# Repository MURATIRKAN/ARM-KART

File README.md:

//*********************************//
ELEKTRONİK SİSTEM TASARIM ÇALIŞMALARI //
GELİŞTİRME KARTLARI-YAZILIM.     //
MURAT IRKAN 2021-2023            //
muratir1975@windowslive.com      //
***********************************

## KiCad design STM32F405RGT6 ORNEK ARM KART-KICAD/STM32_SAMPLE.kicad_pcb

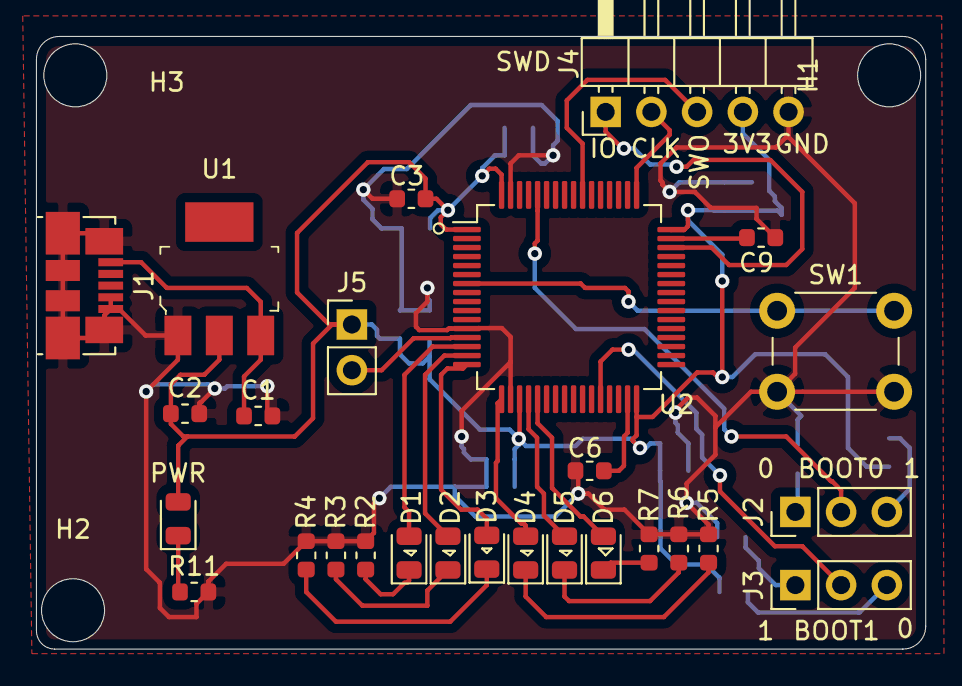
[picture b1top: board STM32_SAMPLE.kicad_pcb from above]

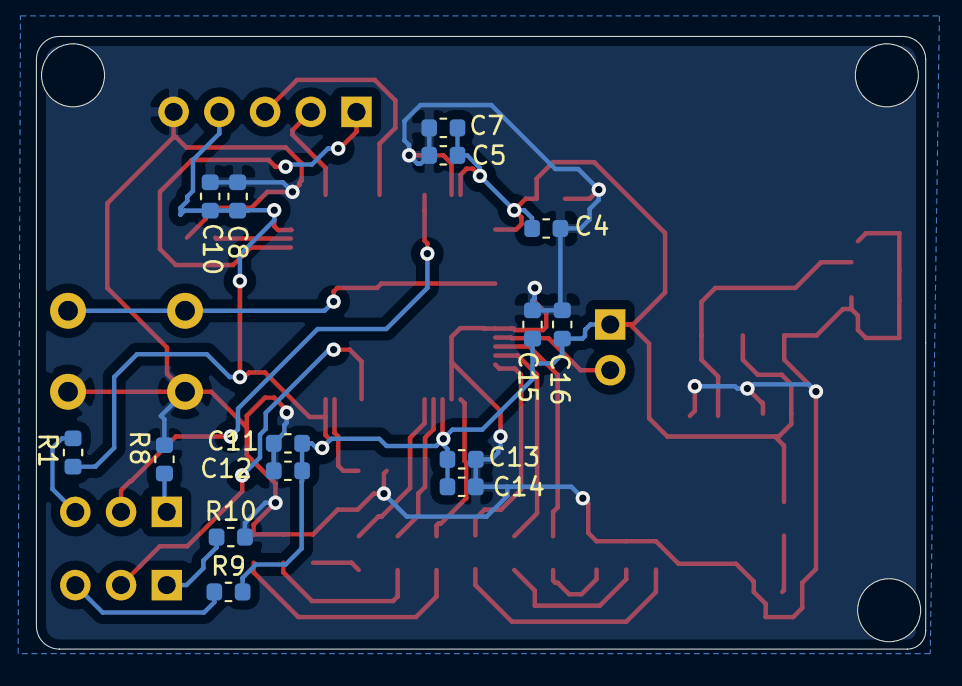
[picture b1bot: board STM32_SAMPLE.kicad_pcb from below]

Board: 2 copper layers, 49.4 x 34.0 mm, 45 parts (15 on the bottom side), 29 nets.

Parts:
C1, C2, C3: 10uF; C_0603_1608Metric
C4, C5, C7, C8, C10, C11, C12, C13, C14, C15: 100nF; C_0603_1608Metric
C6, C9: 2.2uF; C_0603_1608Metric
C16: 1uF; C_0603_1608Metric
D1, D2, D3, D4, D5, D6: LED; LED_0805_2012Metric
H1, H2, H3: MountingHole; MountingHole_3.5mm
J1: USB_B_Micro; USB_Micro-B_Molex_47346-0001
J2, J3: Conn_01x03_Male; PinHeader_1x03_P2.54mm_Vertical
J4: Conn_01x05_Male; PinHeader_1x05_P2.54mm_Horizontal
J5: Conn_01x02_Male; PinHeader_1x02_P2.54mm_Vertical
PWR: LED; LED_0805_2012Metric
R1, R8, R9, R10: 10K; R_0603_1608Metric
R2, R3, R4, R5, R6, R7, R11: 220ohms; R_0603_1608Metric
SW1: SW_Push; SW_PUSH_6mm_H5mm
U1: LM1117-3.3; SOT-223
U2: STM32F405RGTx; LQFP-64_10x10mm_P0.5mm

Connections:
+3V3: C2.1, C3.1, C4.1, C5.1, C7.1, C8.1, C10.1, C11.1, C12.1, C13.1, C14.1, C15.1, C16.1, J4.4, J5.1, PWR.2, R1.2, R9.2, U1.2, U2.1, U2.19, U2.32, U2.48, U2.64
+5V: C1.1, J1.1, U1.3
BOOT0: J2.2, U2.60
BOOT1: J3.2, U2.28
GND: C1.2, C2.2, C3.2, C4.2, C5.2, C6.2, C7.2, C8.2, C9.2, C10.2, C11.2, C12.2, C13.2, C14.2, C15.2, C16.2, J1.4, J1.5, J1.6, J4.5, R2.1, R3.1, R4.1, R5.1, R6.1, R7.1, R8.1, R10.2, R11.2, SW1.2, U1.1, U2.12, U2.18, U2.63
NRST: SW1.1, U2.7
unnamed: C6.1, U2.31
unnamed: C9.1, U2.47
unnamed: D1.1, R2.2
unnamed: D1.2, U2.14
unnamed: D2.1, R3.2
unnamed: D2.2, U2.15
unnamed: D3.1, R4.2
unnamed: D3.2, U2.16
unnamed: D4.1, R5.2
unnamed: D4.2, U2.17
unnamed: D5.1, R6.2
unnamed: D5.2, U2.20
unnamed: D6.1, R7.2
unnamed: D6.2, U2.21
unnamed: PWR.1, R11.1
unnamed: J2.1, R8.2
unnamed: J2.3, R1.1
unnamed: J3.1, R10.1
unnamed: J3.3, R9.1
SWDCLK: J4.2, U2.49
SWDIO: J4.1, U2.46
SWO: J4.3, U2.55
VDDA: J5.2, U2.13

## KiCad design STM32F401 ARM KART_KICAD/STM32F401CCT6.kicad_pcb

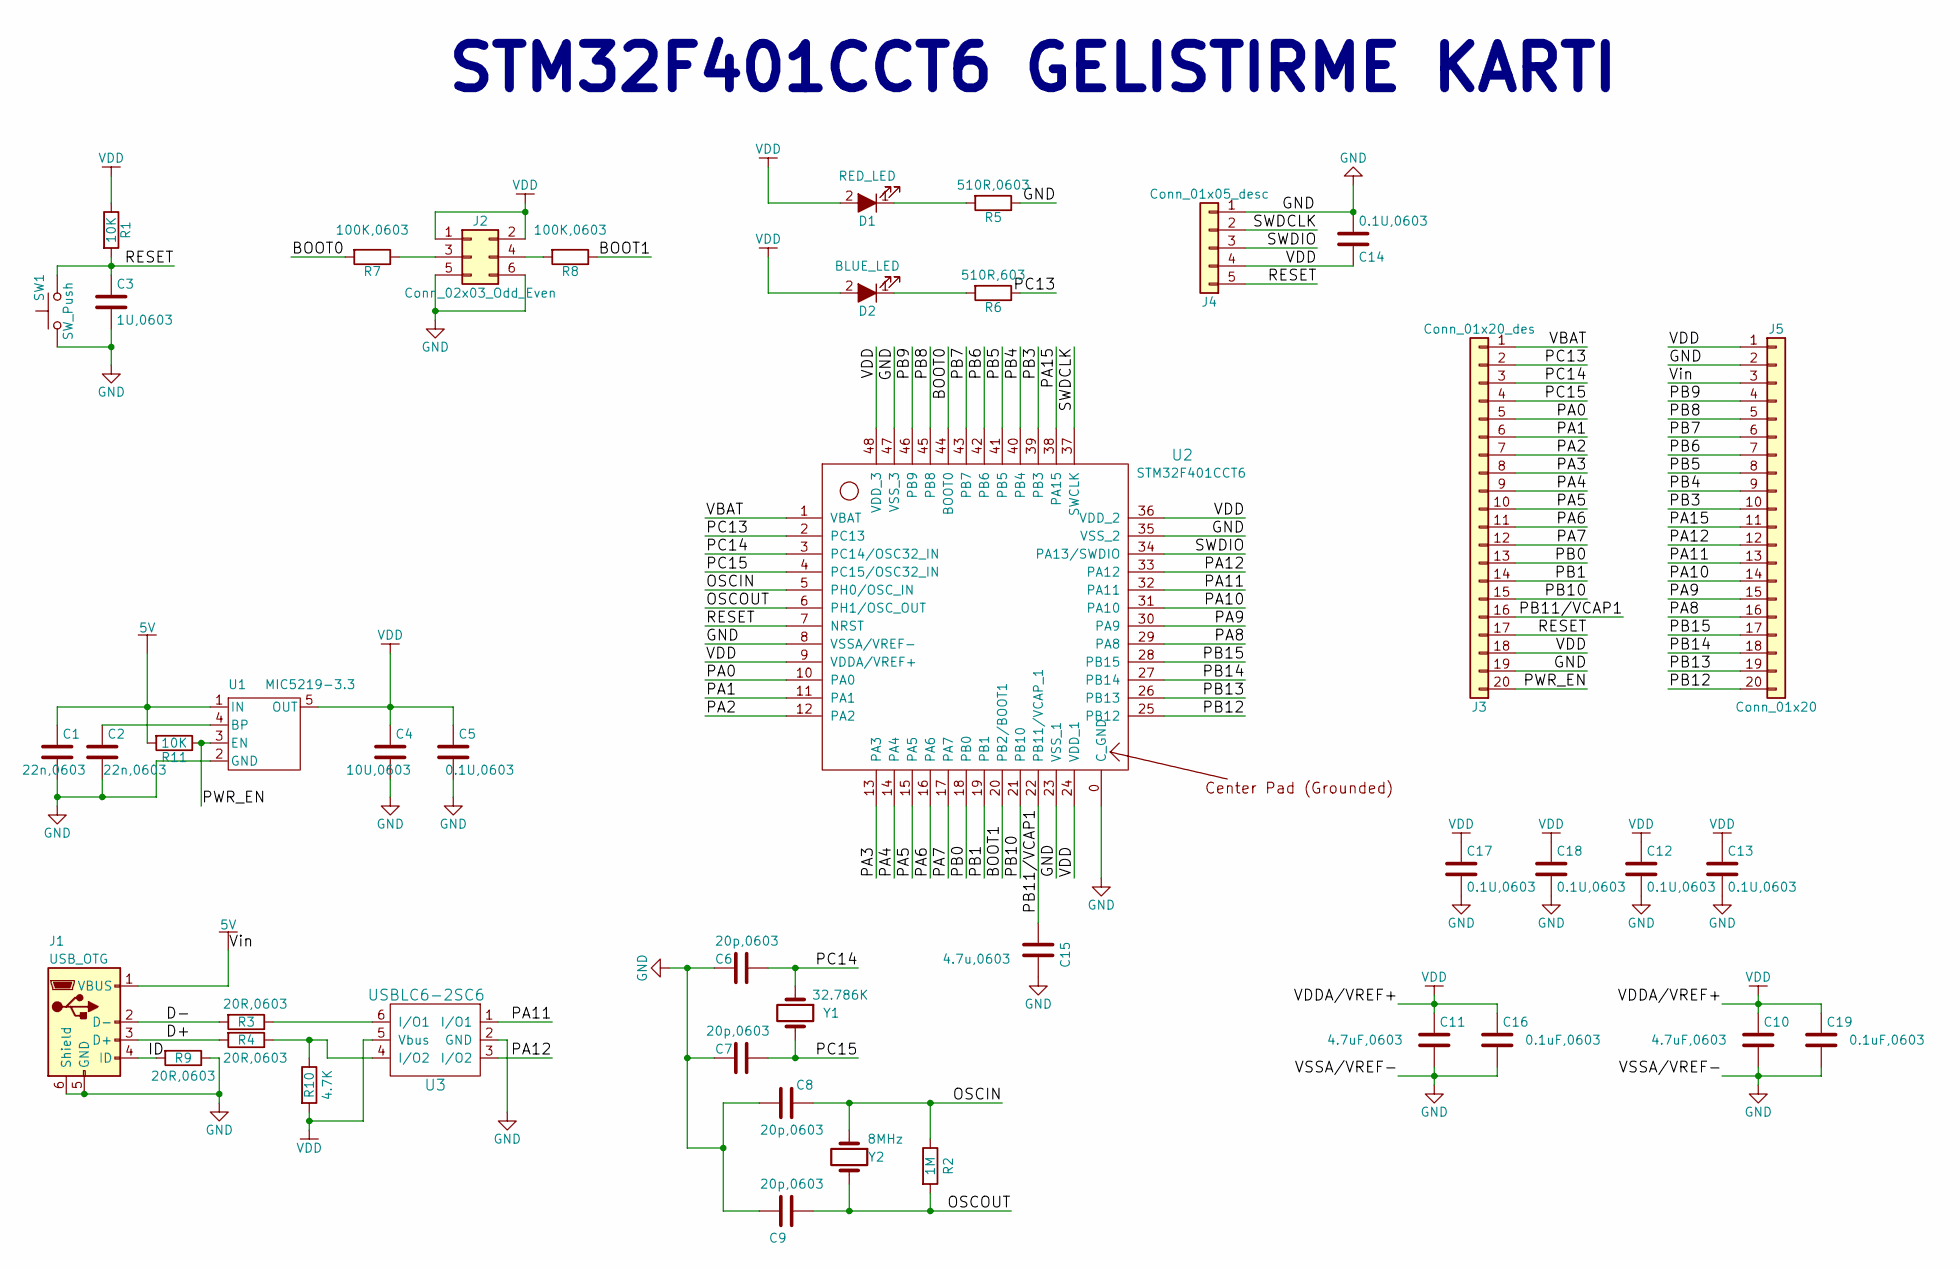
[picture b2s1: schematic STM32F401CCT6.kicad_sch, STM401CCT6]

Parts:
C1, C2: 22n,0603; C_0603
C3: 1U,0603; C_0603
C4: 10U,0603; C_0603
C5, C12, C13, C14, C17, C18: 0.1U,0603; C_0603
C6, C7, C8, C9: 20p,0603; C_0603
C10, C11: 4.7uF,0603; C_0603
C15: 4.7u,0603; C_0603
C16, C19: 0.1uF,0603; C_0603
D1: RED_LED; LED_0805
D2: BLUE_LED; LED_0805
J1: USB_OTG; USB_Micro-B_Molex-105017-0001
J2: Conn_02x03_Odd_Even; Pin_Header_Straight_2x03_Pitch2.54mm
J3: Conn_01x20_des; Pin_Header_Straight_1x20_Pitch2.54mm
J4: Conn_01x05_desc; Pin_Header_Angled_1x05_Pitch2.54mm
J5: Conn_01x20; Pin_Header_Straight_1x20_Pitch2.54mm
R1, R11: 10K; R_0603
R2: 1M; R_0603
R3, R4, R9: 20R,0603; R_0603
R5: 510R,0603; R_0603
R6: 510R,603; R_0603
R7, R8: 100K,0603; R_0603
R10: 4.7K; R_0603
SW1: SW_Push; SW_SPST_TL3342
U1: MIC5219-3.3; SOT-23-5
U2: STM32F401CCT6
U3: USBLC6-2SC6; SOT-23-6
Y1: 32.786K; Crystal_SMD_SeikoEpson_MC306-4pin_8.0x3.2mm
Y2: 8MHz; Crystal_HC49-4H_Vertical

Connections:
+5V: C1.1, J1.1 (VBUS), J5.3, R11.2, U1.1 (IN)
/BOOT0: R7.2, U2.44 (BOOT0)
/BOOT1: R8.1, U2.20 (PB2/BOOT1)
/D+: J1.3 (D+), R4.2
/D-: J1.2 (D-), R3.2
/ID: J1.4 (ID), R9.2
/OSCIN: C8.1, R2.1, U2.5 (PH0/OSC_IN), Y2.1
/OSCOUT: C9.1, R2.2, U2.6 (PH1/OSC_OUT), Y2.2
/PA0: J3.5, U2.10 (PA0)
/PA1: J3.6, U2.11 (PA1)
/PA2: J3.7, U2.12 (PA2)
/PA3: J3.8, U2.13 (PA3)
/PA4: J3.9, U2.14 (PA4)
/PA5: J3.10, U2.15 (PA5)
/PA6: J3.11, U2.16 (PA6)
/PA7: J3.12, U2.17 (PA7)
/PA8: J5.16, U2.29 (PA8)
/PA9: J5.15, U2.30 (PA9)
/PA10: J5.14, U2.31 (PA10)
/PA11: J5.13, U2.32 (PA11), U3.1 (I/O1)
/PA12: J5.12, U2.33 (PA12), U3.3 (I/O2)
/PA15: J5.11, U2.38 (PA15)
/PB0: J3.13, U2.18 (PB0)
/PB1: J3.14, U2.19 (PB1)
/PB3: J5.10, U2.39 (PB3)
/PB4: J5.9, U2.40 (PB4)
/PB5: J5.8, U2.41 (PB5)
/PB6: J5.7, U2.42 (PB6)
/PB7: J5.6, U2.43 (PB7)
/PB8: J5.5, U2.45 (PB8)
/PB9: J5.4, U2.46 (PB9)
/PB10: J3.15, U2.21 (PB10)
/PB11/VCAP1: C15.2, J3.16, U2.22 (PB11/VCAP_1)
/PB12: J5.20, U2.25 (PB12)
/PB13: J5.19, U2.26 (PB13)
/PB14: J5.18, U2.27 (PB14)
/PB15: J5.17, U2.28 (PB15)
/PC13: J3.2, R6.1, U2.2 (PC13)
/PC14: C6.1, J3.3, U2.3 (PC14/OSC32_IN), Y1.1
/PC15: C7.1, J3.4, U2.4 (PC15/OSC32_IN), Y1.2, Y1.4
/PWR_EN: J3.20, R11.1, U1.3 (EN)
/RESET: C3.1, J3.17, J4.5, R1.2, SW1.2, U2.7 (NRST)
/SWDCLK: J4.2, U2.37 (SWCLK)
/SWDIO: J4.3, U2.34 (PA13/SWDIO)
/VBAT: J3.1, U2.1 (VBAT)
/VDD: C4.1, C5.1, C10.1, C11.1, C12.1, C13.1, C14.1, C16.1, C17.1, C18.1, C19.1, D1.2 (A), D2.2 (A), J2.1, J2.2, J3.18, J4.4, J5.1, R1.1, R10.2, U1.5 (OUT), U2.9 (VDDA/VREF+), U2.24 (VDD_1), U2.36 (VDD_2), U2.48 (VDD_3), U3.5 (Vbus)
GND: C1.2, C2.2, C3.2, C4.2, C5.2, C6.2, C7.2, C8.2, C9.2, C10.2, C11.2, C12.2, C13.2, C14.2, C15.1, C16.2, C17.2, C18.2, C19.2, J1.5 (GND), J1.6 (Shield), J2.5, J2.6, J3.19, J4.1, J5.2, R5.1, R9.1, SW1.1, U1.2 (GND), U2.0 (C_GND), U2.8 (VSSA/VREF-), U2.23 (VSS_1), U2.35 (VSS_2), U2.47 (VSS_3), U3.2 (GND)
unnamed: C2.1, U1.4 (BP)
unnamed: D1.1 (K), R5.2
unnamed: D2.1 (K), R6.2
unnamed: J2.3, R7.1
unnamed: J2.4, R8.2
unnamed: R3.1, U3.6 (I/O1)
unnamed: R4.1, R10.1, U3.4 (I/O2)

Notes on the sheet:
STM32F401CCT6 GELISTIRME KARTI

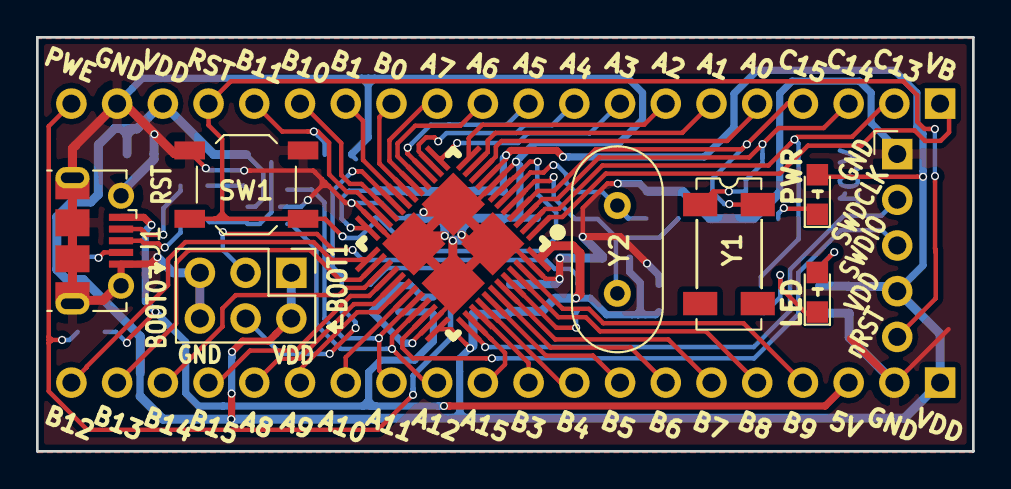
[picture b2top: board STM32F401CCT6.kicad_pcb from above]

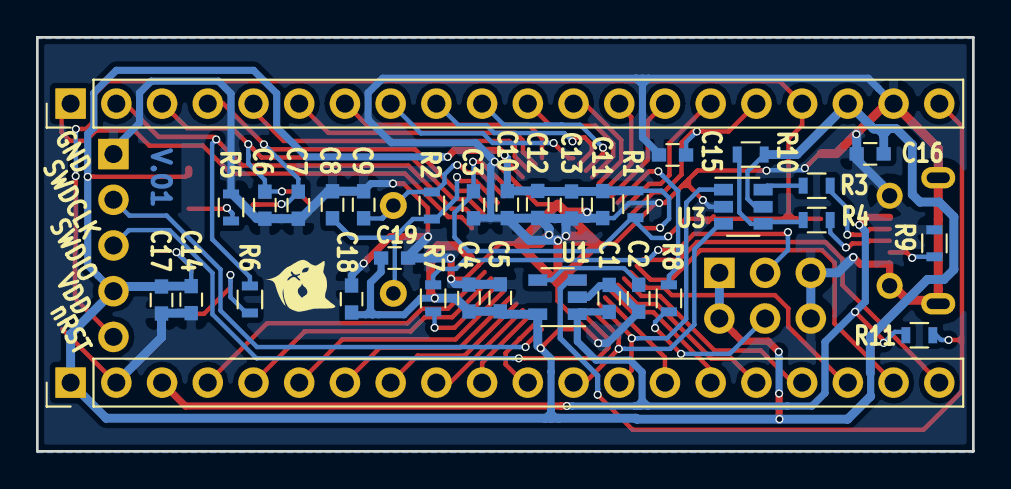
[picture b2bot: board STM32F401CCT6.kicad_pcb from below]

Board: 2 copper layers, 52.0 x 23.0 mm, 47 parts (35 on the bottom side), 54 nets.

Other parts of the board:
Dot: G***; Dot
HS_Crystal: G***; HS_Crystal
LS_Crystal: G***; LS_Crystal
Meow: G***; Meow

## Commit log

2022-09-24 STM32F401CCT6 ARM KART DİZAYN
    PCB VE ŞEMA.
    KİCAD ELEKTRONIK TASARIM PROGRAMI.
    https://www.kicad.org/
2022-09-24 STM32F042x6 ARM TEMEL KARTI
    NOT:KART PINLERI DEGISTIRILDI.!
2022-09-24 STM32F407 ARM GELISTIRME VE INTERNET KARTI
2022-09-24 STM32F042x6 SERİSİ DEMO KART DİZAYN.
    v.1.01
2022-09-26 STM32F405RGT6 ARM KART
2022-09-28 STM32F765VIT6 EAGLE VE DIP TRACE
    TASARLANIRKEN EAGLE TASARIM PROGRAMI VE DIP TRACE PROGRAMLARI KULLANILDI.
    1.https://diptrace.com/tr/
    2.https://www.autodesk.com/products/eagle/free-download
2022-09-29 STM32F401 ARM KEIL KOD
    ARM KEIL 6.18 DERLEYICI KULLANILDI.
2022-10-01 STM32F765VIT ARM KART V.1.02
    GUNCELLEME 9/1/2022
2022-10-02 STMF103CBT6 MINI ARM GELISTIRME KARTI
2022-10-02 stm32f103cbt6 pcb
2022-10-02 STM32F103 ZAMANLAMA VE LED KONTROL
    DERLEYICI KEIL ARM 6.18.
2022-10-08 STM32F103CBT6 TEMEL ARM KART
    ST MICROELEKTRONICS STM32F103CBT6 ARM - CORTEX M3 İŞLEMCİ
2022-10-08 STM32F103 ARM KEIL 6.18 DERLEYİCİ.
    STM32F103 ZAMANLAMA TEST KOD..
2022-10-08 STM32F103 ZAMANLAMA KODLARI.
    KEIL ARM VERSIYON 6.18
2022-10-08 STM32F042
2022-10-08 STM32F765VIT6 ARM CORTEX M7 DEMO.
2022-10-08 STM32F405RGT6 DEMO KART.KICAD TASARIM PROGRAMI.
2022-10-08 STM32F401 ARM CORTEX-M4 MINI
    STM32F401 ARM CORTEX-M4 MİNİ GELİŞTİRME KARTI
    V.1.02
2022-10-08 STM32F ARM KARTLAR.
2022-10-08 STM32F765VIT6 DEMO ARM KART
2022-10-14 STM32F103CBT6 MINI ARM GELİŞTİRME KARTI.
    V.1.01
    6/10/2022
2022-10-14 STM32F103CBT6 MİNİ ARM_CORTEX M3 GELİŞTİRME KARTI.
2022-10-14 STM32F103CBT6 MİNİ ARM CORTEX-M3 GELİŞTİRME KARTI.
    KART AUTODESK VEYA DIP TRACE İLE TASARLANMIŞTIR.
    V.1.02
2022-10-14 STM32F401 ARM GELİŞTİRME KARTI KICAD.
    KICAD ARM GELİŞTİRME KARTI DEMO.
2022-10-15 stm32f103cbt6 V.1.02
    MİNİ STM32F103CBT6 ARM KART...
2022-10-15 Delete STM32F103CBT6 ARM_KART directory
    DIPTRACE ELEKTRONIK TASARIM PROGRAMI
    STM32F103CBT6 PCB DEVRE TASARIMI..
2022-10-15 STM32F103CBT6:DIPTRACE TASARIM PROGRAMI v.1.02
    NOT:DEVRE USB DEN PROGRAMLANIR.STLINK ADAPTORU İLE.
2022-10-16 stm32f103cbt6 MİNİ ARM KART.(JTAG)
    GÜNCELLEME=JTAG-PROGRAMLAMA SOKETİ EKLENDİ.
    MİNİ JTAG SOKET..
2022-10-16 STM32F103CBT6 ARM GELİŞTİRME KARTI.
    JTAG PORTU VE GÜÇ LEDLERİ EKLENDİ.
2022-10-16 DIPTRACE TASARIM PROGRAMI.
    STM32F103CBT6 ARM-CORTEX M3 GELİŞTİRME KARTI.
    V.1.06 LEDLER VE JTAG SOKET EKLENDİ(MİNİ)
2022-10-17 STM32F103CBT6 DIPTRACE VE EAGLE TASARIM.
    MALZEME LİSTESİ EXCEL,GÜÇ LEDLERİ,MİNİ JTAG EKLENDİ.
    DELİKLER 2mm BOYUTUNDA TASARLANDI.
    V.1.07
2023-01-22 PIC18F44K22 KART
    PIC18F44K22 GELİŞTİRME KARTI..
2023-01-26 STM32F405RGT6V ARM KART
2023-01-26 yapay zeka tanıtımı
2023-01-30 STM32F405RGT6 ARM KART PCB
2023-01-30 STM32F405RGT6 AUTODESK EAGLE
2023-01-31 ARDUINO SICAKLIK VE ISIK TEST
2023-01-31 STM32F407 ARM VE INTERNET
2023-01-31 STM32F103CBT6 MINI ARM KART
    V.1.02
2023-01-31 ARDUINO SICAKLIK_ISIK KOD
2023-02-01 ARDUINO TOSHIBA TBN6612FNG MOTOR SURUCU
2023-02-01 ARDUINO BOSCH BME280 SENSOR
2023-02-01 STM32F405 VE 407 DOKUMAN
2023-02-01 ARDUINO DHT22 SENSOR
2023-02-01 STM32 LM35 VE LCD
2023-02-01 STM32F103 ARM KEIL LCD EKRAN
2023-02-01 STM32F103 AUTODESK EAGLE PCB VE SEMA
2023-02-01 arduıno l298 motor
2023-02-04 PIC18F44K22 KART
    MICRO-C ORNEK
2023-02-04 STMF103CBT6 ARM KART
2023-02-04 MICRO C PIC16 DC18B20 SENSOR
2023-02-07 STM32F405RGT6 ARM GELİŞTİRME KARTI
2023-02-07 PIC18F44K50 VE 45K50 GELİŞTİRME KARTI
2023-02-07 STM32F103CBT6 MINI ARM KART
2023-02-08 STM32F401CCT6 ARM VE ORNEK KiCad 6.0
2023-02-08 STM32F401CB PROTEUS VE KOD
2023-02-08 STM32F401CB KART/ARM KEIL KOD VE PROTEUS
2023-02-08 PIC16F877 MICRO_C LM35 SENSOR
2023-02-08 PIC18F44K22 VEYA PIC18F45K50 KART
    LM35 MICRO_C DERLEYICI
2023-02-08 STM32F407 ARM GELISTIRME VE INTERNET
2023-02-08 STM32F103CBT6 MINI ARM GELISTIRME KARTI
2023-02-08 STM32F401CB ARM GELISTIRME KARTI
2023-02-08 C & PYTHON KİTAP
2023-02-08 BANANA PI ARM BILGISAYAR
2023-02-08 CIZGI IZLEYEN ROBOT TASARIMI SOLIDWORKS
    ARDUINO NANO
2023-02-08 STM32F407 BOSCH BME280 SENSOR
2023-02-08 STM32 KUTUPHANELERI
2023-02-08 STM32F765VIT6 ARM GELISTIRME KARTI
2023-02-08 STM32 ARM KAMERA KEIL ARM DERLEYICI
2023-02-08 STM32 KAMERA
2023-02-08 STM32 KAMERA OV9655 ARM KEIL
2023-02-08 STM32 MICRO PYTHON KODLAR
2023-02-09 STM32F103 DC MOTOR KONTROL ARM KEIL
2023-02-09 ARDUINO HAVA ISTASYONU SOLIDWORKS TASARIM DEMO
2023-02-15 BLDC MOTOR KONTROL DİZAYN
2023-02-15 ARM KEIL STM32F103 STEP MOTOR VE PROTEUS
2023-02-17 MPU6050 PUSULA VE İVME SENSORÜ
2023-02-18 ARDUINO HAVA İSTASYON PROTEUS v8.13
2023-02-18 ARDUINO HAVA İSTASYON-PROTEUS v8.13
2023-02-18 ARDUINO BASINC OLCUM CIHAZI
2023-02-21 PIC18F44K22
2023-02-23 STM32F103CBT6 GELISTIRME KARTI
2023-02-23 PYTHON TERMAL KAMERA MLX90640
2023-02-26 STM32F401CCT6 ARM GELISTIRME KART v.1.01
    KICAD TASARIM PROGRAMI
2023-02-26 STM32F401CCT6 ARM CORTEX M4 GELISTIRME KARTI
    V.1.02
2023-02-26 STM32 ARM BLDC MOTOR KONTROL SİSTEMİ
2023-02-26 ARDUINO NANO CIZGI IZLEYEN ROBOT SOLIDWORKS 2018
2023-02-26 STM32F405RGT6 ARM YAPAY ZEKA KARTI
2023-02-26 STM32F765VIT6 ARM GELSITIRME KARTI
    DEMO VERSIYON
2023-02-26 BEAGLEBONE BLACK I2C BAGLANTI KUTUPHANESI
2023-05-23 MICROCHIP ATSAM51G ARM-32 BIT GELISTIRME KARTI
    REV .1.02
2023-05-23 MICROCHIP ATSAM51G ARM GELİŞTİRME KARTI
    REV 1.2.1
2023-05-23 STM32F405RG ARM VE YAPAY ZEKA KARTI
2023-05-23 STM32F405RG ARM VE YAPAY ZEKA GELİŞTİRME KARTI
    REV 1.00.1
2023-05-23 STM32F407xx ARM CORTEX M4 GELİŞTİRME KARTI
    LOKAL İNTERNET KARTI.
    REV.1.01
2023-05-23 STM32F401 ARM CORTEX M4 KART
    REV.1.5
2023-05-23 MICROCHIP PIC18F44K22 KONTROL KARTI
    REV.1.03
2023-05-24 DIPTRACE MLX90640 TERMAL KAMERA MODÜLÜ ŞEMA
2023-05-24 LM3671-600miliAMPER regulatör
2023-05-24 ADAFRUIT TRINKET KART SERİSİ
2023-05-30 STM32F103CB ARM GELİŞTİRME KARTI
2023-05-30 NXP LPC1768 MCU GELİŞTİRME KARTI
2023-05-30 NXP LPC1343 GELİŞTİRME KARTI
2023-05-30 MICROCHIP ENJ424J600 NETWORK KARTI
2023-06-02 PIC24FJ256GB106 VE LAN GELİŞTİRME KARTI v.1.03
2023-06-02 PIC24FJ256GB106 16-BIT MCU VE LAN KARTI
    VERSIYON 1.1.2
2023-06-02 ENC424J600 NETWORK(LAN 10/100 MEGABIT) KARTI
    V.1.01
2023-06-02 STM32F407VE AR GELİŞTİRME VE NETWORK KARTI
2023-06-02 ENC424J600 LAN KARTI 10/100 MEGABIT
2023-06-02 MICROCHIP PIC18F44K22 GELİŞTİRME KARTI
    v.1.2
2023-06-02 ARDUINO STEREO RADYO + 35mW AM-FI KARTI
2023-06-03 PIC18F44K22 VE PIC18F45K50 GELİŞTİRME KARTI
    v.1.2
2023-06-03 CNC MAKİNESİ KONTROL KARTI
    A4988 STEP MOTOR 2x3 TOPLAM 6 AMPER,ATMEGA 328P MCU+ USB
2023-06-04 ARM CORTEX-M4 STM32F405RG GELİŞTİRME KARTI
    v.1.2 devre şeması ve DATASHEET.
    DEMO VERSİYONDUR.
2023-06-04 MICROCHIP ATSAMD51G ARM CORTEX M4 KART
    rev.1.00
2023-06-04 CNC MAKİNESİ KONTROL KARTI ATMEGA328P MCU
    A4988 STEP MOTOR 3-EKSEN 2 AMPER
2023-06-04 PIC18F44K22 VEYA PIC18F45K50 GELİŞTİRME KARTI.
2023-06-04 CNC MAKİNE KONTROL KARTI ARMEGA328P v.1.02
    demo kart 3-EKSEN 2 AMPER A4988 STEP MOTOR
2023-06-05 TEMEL ROBOT MODEL SOLIDWORK 2018
2023-06-05 STM32F407VE ARM GELİŞTİRME KARTI PCB
2023-06-05 MSP430 GELİŞTİRME KARTI
2023-06-05 STM32F030F4x ARM CORTEX-M0 DEVRE ŞEMASI PDF
    DİĞER ELEKTRONİK PARÇALAR.
2023-06-05 PARALLAX BASIC STAMP 2 DEVRE
2023-06-06 STM32F405RGT6 ARM GELİŞTİRME KARTI
    REGULATOR AMS1117 0.8 AMPER TOPLAM AKIM
2023-06-06 CNC KONTROL KARTI PCB A4988 3-EKSEN 2 AMPER
    ücretli demo versiyondur.
2023-06-06 CNC MAKİNESİ KONTROL KARTI A4988 3-EKSEN 2AMPER
    REV.1.03
2023-06-07 CNC MAKİNESİ KONTROL KARTI 2 AMPER STEP MOTOR
    REV.1.00
2023-06-07 TEXAS INSTRUMENTS DRV8833 DC MOTOR KONTROL PCB
2023-06-08 TI DRV8833 DC VE STEP MOTOR SÜRÜCÜ KARTI
2023-06-08 DRV8833: 2 DC-1 STEP MOTOR SÜRÜCÜ KARTI
2023-06-08 MICROCHIP HASSAS SICAKLIK SENSOR MCP9808
    SENSOR KARTI
2023-06-08 DRV8313 PYTHON BLCD MOTOR SÜRÜCÜSÜ ÖRNEK KOD
2023-06-08 TI DRV8871 TEK DC MOTOR 3.6 AMPER MOTOR SÜRÜCÜSÜ
2023-06-08 TI DRV8871 2-3.6 AMPER TEK DC MOTOR SÜRÜCÜSÜ
2023-06-09 MICROCHIP PIC18F45K50 GELİŞTİRME KARTI
    REV.1.02 SATILIK:760 TL
2023-06-11 PIC18F45K50 GELİŞTİRME KARTI(rev.1.02)
2023-06-11 ATSAMD51G ARM CORTEX M4 KART
2023-06-12 NETWORK(LAN) ENC424J600 10/100 MEGABIT
    rev.1.03
2023-06-12 MC33886 DC VE SELENOID MOTOR KONTROL KARTI
    ŞEMA PDF.
2023-06-12 ATMEL ATSAM21G ARM CORTEX KART
2023-06-12 ATSAM21G ARM CORTEX GELİŞTİRME KARTI
    rev.1.02
2023-06-13 NETWORK KART (ENC424J600 10/100)
    rev.1.02
2023-06-13 ÖN MUHASEBE 2.3.21 GÜNCELLEME.(13/06/2023)
    PRO VE LITE VERSİYON OLARAK.
2023-06-13 STM32F405RGT6 ARM-CORTEX M4 DEVRE ŞEMA v.1.02
2023-06-13 STM32F407VE ARM KART
    BU KART SATILIKTIR. REV.1.01
2023-06-14 ENJ424J600 NETWORK TASARIM
    REV.1.02
2023-06-16 TEXAS INSTRUMENTS DRV8833 MOTOR SÜRÜCÜ
    EAGLE ŞEMA VE PCB.
2023-06-17 ATMEL ATTINY85 MCU MİKRO-KART rev:1.00
2023-06-17 ATTINY85-PCB rev.1.01
2023-06-18 PIC24FJ256GB106_16-BIT MCU VE LAN
    rev.1.01
2023-06-18 PIC18F45K50 VEYA PIC18F44K22 KART
    REV.1.01
2023-07-13 PIC18F44K22 VEYA PIC18F45K50 KART
    REV.1.01
2023-10-30 STM32F103CBT6 ARM-KART DİZAYN
    ST MICROELEKTRONICS
2023-10-30 PIC24 + NETWORK KART PIC24FJ256GB106 16-BIT
2023-10-30 AT91SAM MICROCHIUP ARC-LINUX KART
    ARC LINUX MICROCHIP ARM-KART
2023-10-30 PIC16F1938 GELİŞTİRME KARTI 8-BIT v1.01
2023-11-01 APOLLO 3 ARM-CORTEX M4 MCU DİZAYN+ PCB
2023-11-18 MODEL-DEMO
2023-11-18 PROTEUS 8.13 ARDUINO HAVA İSTASYONU
2023-11-27 RASPBERRY PI 2040 DEMO :REV.1.00
    ORNEK RASPBERRY PI 2040 DEVRE TASARIMI
2023-11-27 RASPBERRY PI 2040 ÖRNEK DEVRE
    rev:1.00
2023-11-27 RASPBERRY PI 2040 ÖRNEK TASARIM: REV.1.01
2024-01-22 STM32F407ZET6 ARM GELISTIRME KARTI REV.E VE F
2024-02-02 ALLWINNER A20 ARM LINUX ŞEMA
    REV.B
2024-02-02 ALLWINNER A33 ARM CPU ANDROID TABLET
    REV. VE B
2024-02-02 TEXAS INSTRUMENTS AM3352 ARM LINUX SİSTEM
    REV A ..
2024-02-03 AUTODESK EAGLE ARM BILGISAYAR ANDROID-LINUX
    REV/- A VE C
2024-02-03 PC RESIM ALLWINNER H3
2024-02-06 ANDROID VE LINUX ONBOARD BİLGİSAYAR(MURAT IRKAN)
    REV A VE B
2024-02-19 ST MICROELEKTRONICS ROBOT SİSTEMLERİ PDF
2024-02-19 ROBOT ARABA TASARIM SOLIDWORKS 2018
2024-02-21 NXP İ.MX233 MPU TASARIM rev.e
2024-02-21 CİZGİ İZLEYEN ROBOT SOLIDWORKS 2018
2024-02-21 RAZER OYUNCU MOUSE DEATH ADDER V2 PRO
    SOLIDWORKS 2018
2024-03-03 ALLWINNER H3 LINUX-ANDROID ONBOARD BİLGİSAYAR
    REVİZYON C. v.1.01
2024-03-07 ALLWINNER A64 LINUX SERVER-PC
    REV.A VE REV.B
2024-03-07 ALWINNER A64 LINUX SERVER VE EKİPMAN
    REV.A VE B
2024-03-08 AUTODESK EAGLE ALLWINNER A13 MINI-PC
    REV.C
2024-03-08 A13 DATASHEET-BİLGİ DÖKÜMAN
2024-04-01 NXP-IM233 SİSTEM TASARIM
2024-04-01 ALLWINNER H3 ARM BİLGİSAYAR TASARIM
    LINUX VE ANDROID SİSTEM
2024-04-01 PIC32 32-BIT KONTROL KARTI AUTODESK EAGLE
    REV.1.1
2024-04-06 Create INTEL-LGA1151 PLATFORM
2024-04-06 INTEL LGA1151 PLATFORM
2024-04-06 NVIDIA RTX3080 10GIGABYTE GRAFİK KART DEVRES
2024-04-06 RTX3080 10GIGABYTE
2024-04-06 AMD RX580 8-GIGABYTE
    GIGABYTE AURUS GRAFİK KART
2024-04-06 GIGABYTE-NVIDIA RX3070 8GIGABYTE GRAFİK KART
2024-04-24 ARM OYUN KONSOL PROJESİ
    MURAT IRKAN 2023 REV.B
    AÇIK KAYNAK DONANIM PROJESİ
2024-05-04 ALLWIINER A20 LINUX PC-PCB+ŞEMA REV.A
2024-05-04 ALLWINNER A20 ARM BİLGİSAYAR DEVRE ŞEMASI +PCB
    REV.A VE B
2024-05-10 ST MICROELECTRONICS STM32F407ZET6-PCB REV.C
    STM32F407ZET6 DIPTRACE PCB TASARIM + 3D TASARIM
2024-05-29 A20-PYTHON LEDYAK
2024-06-05 i.mx233 MPU NANO KART
    REV.A
